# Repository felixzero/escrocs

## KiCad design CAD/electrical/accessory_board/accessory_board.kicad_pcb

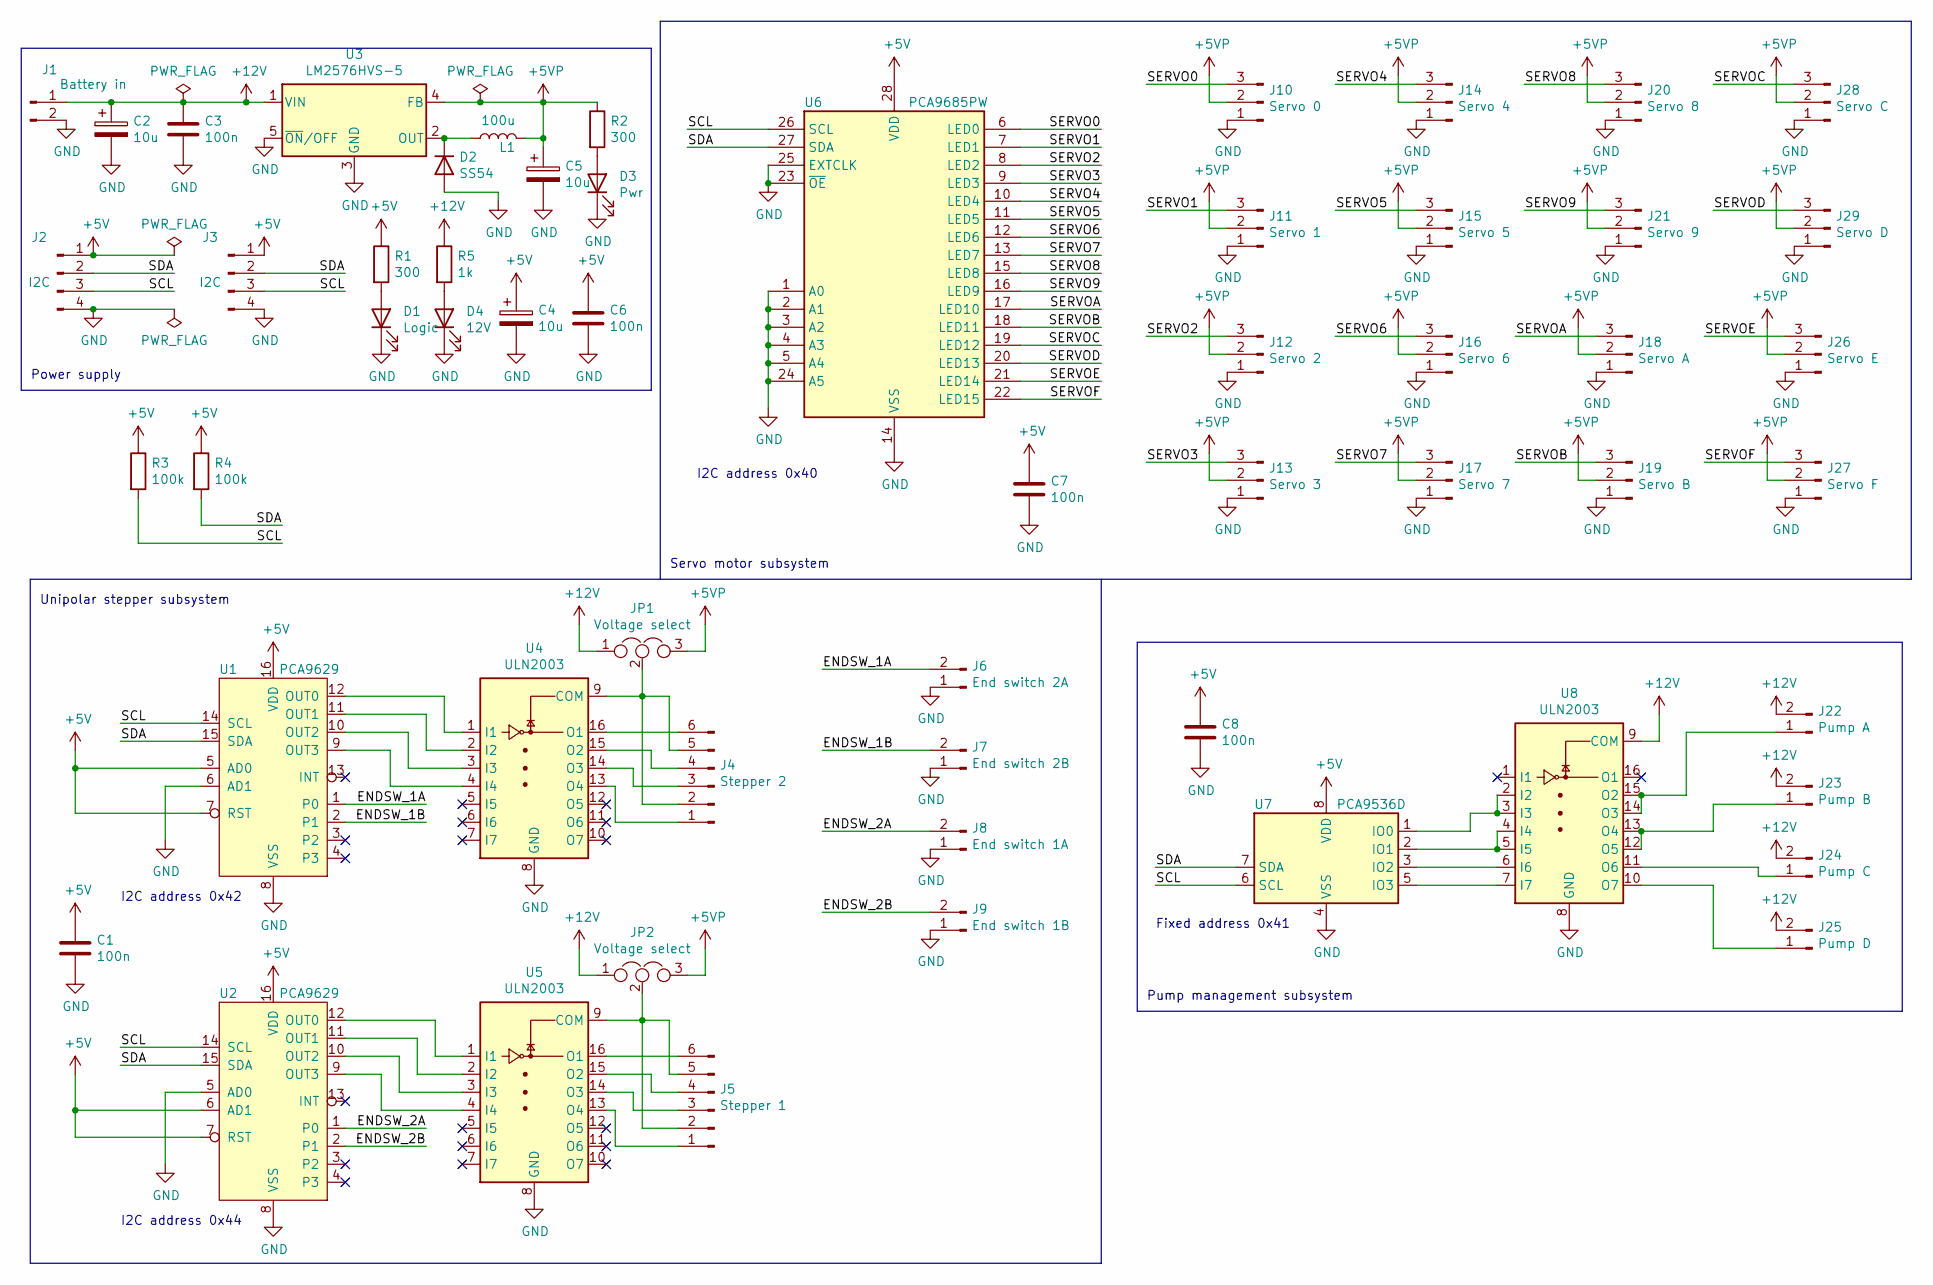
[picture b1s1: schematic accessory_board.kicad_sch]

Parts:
C1, C3, C6, C7, C8: 100n; C_1206_3216Metric_Pad1.33x1.80mm_HandSolder
C2, C4, C5: 10u; CP_Radial_D5.0mm_P2.00mm
D1: Logic; LED_D3.0mm
D2: SS54; D_SMB_Handsoldering
D3: Pwr; LED_D3.0mm
D4: 12V; LED_D3.0mm
J1: Battery in; BarrelJack_Horizontal
J2, J3: I2C; Molex_KK-254_AE-6410-04A_1x04_P2.54mm_Vertical
J4: Stepper 2; Molex_KK-254_AE-6410-06A_1x06_P2.54mm_Vertical
J5: Stepper 1; Molex_KK-254_AE-6410-06A_1x06_P2.54mm_Vertical
J6: End switch 2A; Molex_KK-254_AE-6410-02A_1x02_P2.54mm_Vertical
J7: End switch 2B; Molex_KK-254_AE-6410-02A_1x02_P2.54mm_Vertical
J8: End switch 1A; Molex_KK-254_AE-6410-02A_1x02_P2.54mm_Vertical
J9: End switch 1B; Molex_KK-254_AE-6410-02A_1x02_P2.54mm_Vertical
J10: Servo 0; Molex_KK-254_AE-6410-03A_1x03_P2.54mm_Vertical
J11: Servo 1; Molex_KK-254_AE-6410-03A_1x03_P2.54mm_Vertical
J12: Servo 2; Molex_KK-254_AE-6410-03A_1x03_P2.54mm_Vertical
J13: Servo 3; Molex_KK-254_AE-6410-03A_1x03_P2.54mm_Vertical
J14: Servo 4; Molex_KK-254_AE-6410-03A_1x03_P2.54mm_Vertical
J15: Servo 5; Molex_KK-254_AE-6410-03A_1x03_P2.54mm_Vertical
J16: Servo 6; Molex_KK-254_AE-6410-03A_1x03_P2.54mm_Vertical
J17: Servo 7; Molex_KK-254_AE-6410-03A_1x03_P2.54mm_Vertical
J18: Servo A; Molex_KK-254_AE-6410-03A_1x03_P2.54mm_Vertical
J19: Servo B; Molex_KK-254_AE-6410-03A_1x03_P2.54mm_Vertical
J20: Servo 8; Molex_KK-254_AE-6410-03A_1x03_P2.54mm_Vertical
J21: Servo 9; Molex_KK-254_AE-6410-03A_1x03_P2.54mm_Vertical
J22: Pump A; Molex_KK-254_AE-6410-02A_1x02_P2.54mm_Vertical
J23: Pump B; Molex_KK-254_AE-6410-02A_1x02_P2.54mm_Vertical
J24: Pump C; Molex_KK-254_AE-6410-02A_1x02_P2.54mm_Vertical
J25: Pump D; Molex_KK-254_AE-6410-02A_1x02_P2.54mm_Vertical
J26: Servo E; Molex_KK-254_AE-6410-03A_1x03_P2.54mm_Vertical
J27: Servo F; Molex_KK-254_AE-6410-03A_1x03_P2.54mm_Vertical
J28: Servo C; Molex_KK-254_AE-6410-03A_1x03_P2.54mm_Vertical
J29: Servo D; Molex_KK-254_AE-6410-03A_1x03_P2.54mm_Vertical
JP1, JP2: Voltage select; PinHeader_1x03_P2.54mm_Vertical
L1: 100u; L_Radial_D24.4mm_P23.70mm_muRATA_1400series
R1, R2: 300; R_1206_3216Metric_Pad1.30x1.75mm_HandSolder
R3, R4: 100k; R_1206_3216Metric_Pad1.30x1.75mm_HandSolder
R5: 1k; R_1206_3216Metric_Pad1.30x1.75mm_HandSolder
U1, U2: PCA9629; TSSOP-16_4.4x5mm_P0.65mm
U3: LM2576HVS-5; TO-263-5_TabPin3
U4, U5, U8: ULN2003; SO-16_3.9x9.9mm_P1.27mm
U6: PCA9685PW; TSSOP-28_4.4x9.7mm_P0.65mm
U7: PCA9536D; SOIC-8_3.9x4.9mm_P1.27mm

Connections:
+5V: C1.1, C4.1, C6.1, C7.1, C8.1, J2.1, J3.1, R1.1, R3.1, R4.1, U1.5 (AD0), U1.7 (RST), U1.16 (VDD), U2.6 (AD1), U2.7 (RST), U2.16 (VDD), U6.28 (VDD), U7.8 (VDD)
+5VP: C5.1, J10.2, J11.2, J12.2, J13.2, J14.2, J15.2, J16.2, J17.2, J18.2, J19.2, J20.2, J21.2, J26.2, J27.2, J28.2, J29.2, JP1.3, JP2.3, L1.2, R2.1, U3.4 (FB)
+12V: C2.1, C3.1, J1.1, J22.2, J23.2, J24.2, J25.2, JP1.1, JP2.1, R5.1, U3.1 (VIN), U8.9 (COM)
/ENDSW_1A: J6.2, U1.1 (P0)
/ENDSW_1B: J7.2, U1.2 (P1)
/ENDSW_2A: J8.2, U2.1 (P0)
/ENDSW_2B: J9.2, U2.2 (P1)
/SCL: J2.3, J3.3, R3.2, U1.14 (SCL), U2.14 (SCL), U6.26 (SCL), U7.6 (SCL)
/SDA: J2.2, J3.2, R4.2, U1.15 (SDA), U2.15 (SDA), U6.27 (SDA), U7.7 (SDA)
/SERVO0: J10.3, U6.6 (LED0)
/SERVO1: J11.3, U6.7 (LED1)
/SERVO2: J12.3, U6.8 (LED2)
/SERVO3: J13.3, U6.9 (LED3)
/SERVO4: J14.3, U6.10 (LED4)
/SERVO5: J15.3, U6.11 (LED5)
/SERVO6: J16.3, U6.12 (LED6)
/SERVO7: J17.3, U6.13 (LED7)
/SERVO8: J20.3, U6.15 (LED8)
/SERVO9: J21.3, U6.16 (LED9)
/SERVOA: J18.3, U6.17 (LED10)
/SERVOB: J19.3, U6.18 (LED11)
/SERVOC: J28.3, U6.19 (LED12)
/SERVOD: J29.3, U6.20 (LED13)
/SERVOE: J26.3, U6.21 (LED14)
/SERVOF: J27.3, U6.22 (LED15)
GND: C1.2, C2.2, C3.2, C4.2, C5.2, C6.2, C7.2, C8.2, D1.1 (K), D2.2 (A), D3.1 (K), D4.1 (K), J1.2, J2.4, J3.4, J6.1, J7.1, J8.1, J9.1, J10.1, J11.1, J12.1, J13.1, J14.1, J15.1, J16.1, J17.1, J18.1, J19.1, J20.1, J21.1, J26.1, J27.1, J28.1, J29.1, U1.6 (AD1), U1.8 (VSS), U2.5 (AD0), U2.8 (VSS), U3.3 (GND), U3.5 (~ON/OFF), U4.8 (GND), U5.8 (GND), U6.1 (A0), U6.2 (A1), U6.3 (A2), U6.4 (A3), U6.5 (A4), U6.14 (VSS), U6.23 (~OE), U6.24 (A5), U6.25 (EXTCLK), U7.4 (VSS), U8.8 (GND)
unnamed: D1.2 (A), R1.2
unnamed: D2.1 (K), L1.1, U3.2 (OUT)
unnamed: D3.2 (A), R2.2
unnamed: D4.2 (A), R5.2
unnamed: J4.1, U4.13 (O4)
unnamed: J4.2, J4.5, JP1.2, U4.9 (COM)
unnamed: J4.3, U4.14 (O3)
unnamed: J4.4, U4.15 (O2)
unnamed: J4.6, U4.16 (O1)
unnamed: J5.1, U5.13 (O4)
unnamed: J5.2, J5.5, JP2.2, U5.9 (COM)
unnamed: J5.3, U5.14 (O3)
unnamed: J5.4, U5.15 (O2)
unnamed: J5.6, U5.16 (O1)
unnamed: J22.1, U8.14 (O3), U8.15 (O2)
unnamed: J23.1, U8.12 (O5), U8.13 (O4)
unnamed: J24.1, U8.11 (O6)
unnamed: J25.1, U8.10 (O7)
unnamed: U1.9 (OUT3), U4.4 (I4)
unnamed: U1.10 (OUT2), U4.3 (I3)
unnamed: U1.11 (OUT1), U4.2 (I2)
unnamed: U1.12 (OUT0), U4.1 (I1)
unnamed: U2.9 (OUT3), U5.4 (I4)
unnamed: U2.10 (OUT2), U5.3 (I3)
unnamed: U2.11 (OUT1), U5.2 (I2)
unnamed: U2.12 (OUT0), U5.1 (I1)
unnamed: U7.1 (IO0), U8.2 (I2), U8.3 (I3)
unnamed: U7.2 (IO1), U8.4 (I4), U8.5 (I5)
unnamed: U7.3 (IO2), U8.6 (I6)
unnamed: U7.5 (IO3), U8.7 (I7)

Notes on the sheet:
Fixed address 0x41
I2C address 0x42
I2C address 0x40
I2C address 0x44
Pump management subsystem
Power supply
Servo motor subsystem
Unipolar stepper subsystem

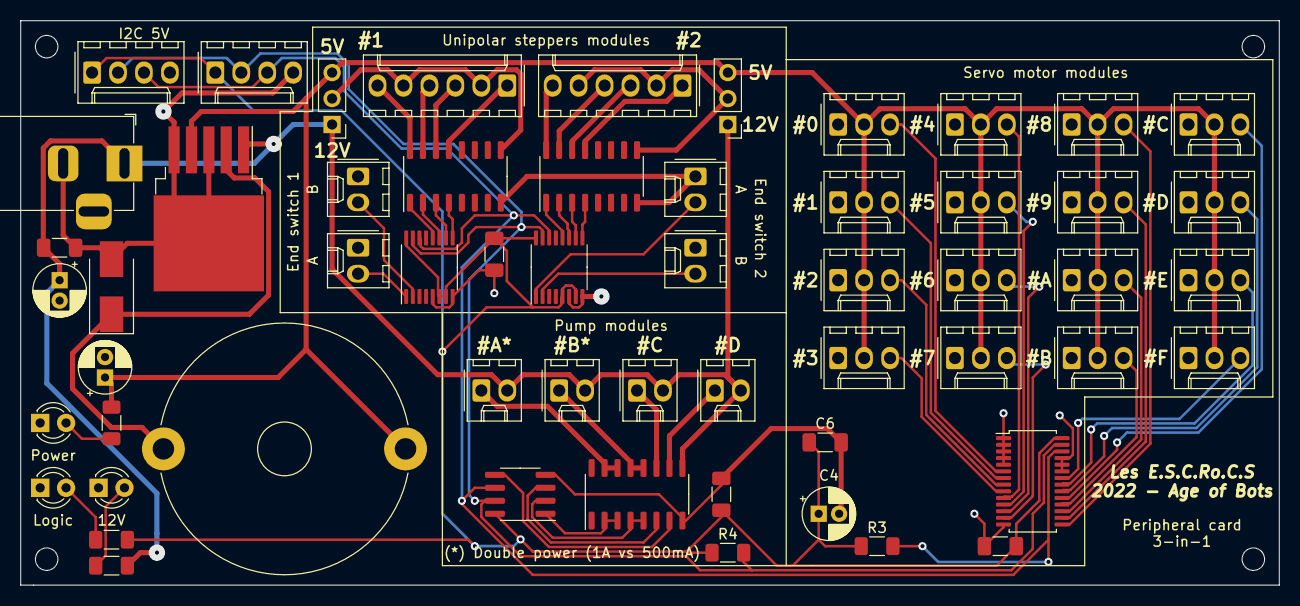
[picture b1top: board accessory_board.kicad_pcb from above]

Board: 2 copper layers, 123.2 x 55.2 mm, 57 parts (0 on the bottom side), 56 nets.

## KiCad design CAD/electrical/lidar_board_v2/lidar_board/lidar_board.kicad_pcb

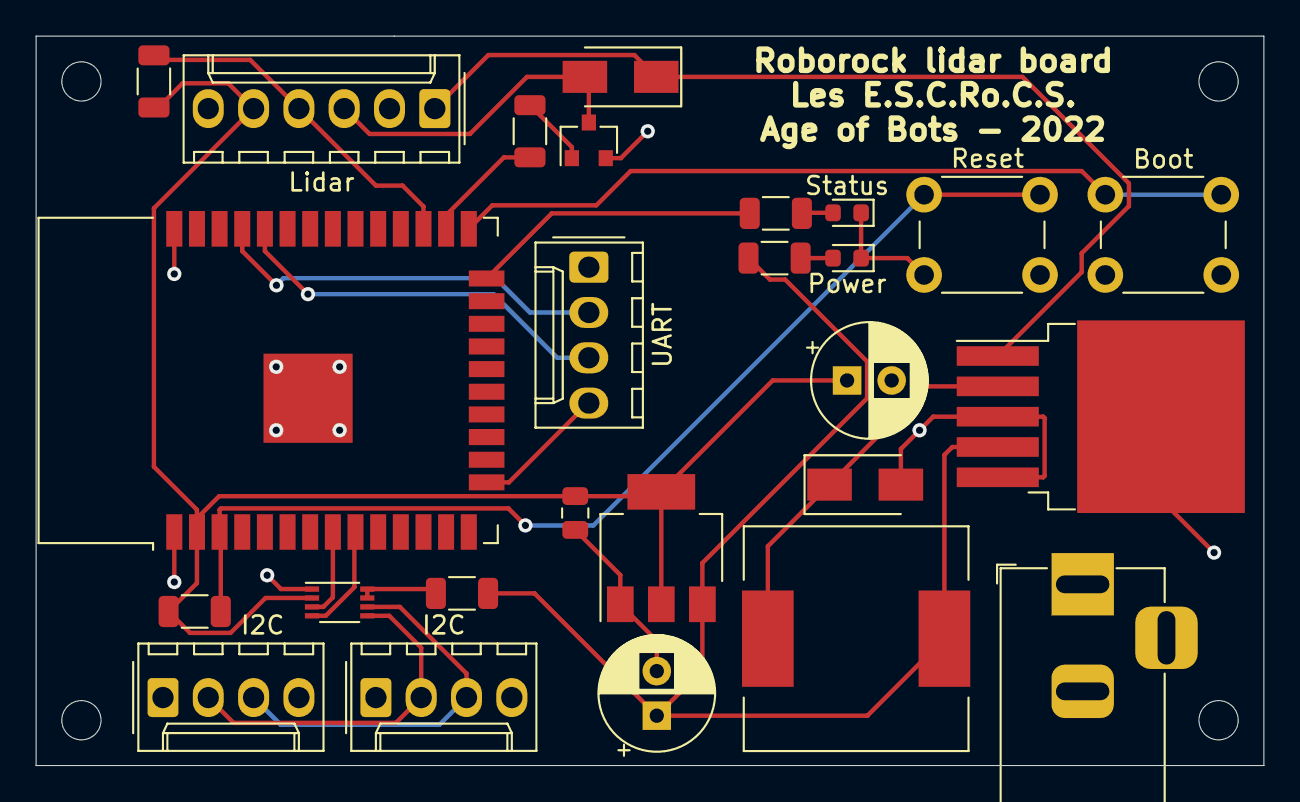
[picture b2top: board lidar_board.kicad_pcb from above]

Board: 2 copper layers, 68.8 x 40.9 mm, 26 parts (0 on the bottom side), 21 nets.

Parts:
Boot: Boot; SW_PUSH_6mm
C1, C2: 10u; CP_Radial_D6.3mm_P2.50mm
C3: 100n; C_0805_2012Metric
D1, D4: SS54; D_SMA
I2C, I2C#2: I2C bus; Molex_KK-254_AE-6410-04A_1x04_P2.54mm_Vertical
J1: 12V in; BarrelJack_Horizontal
L1: 100u; L_12x12mm_H6mm
Lidar: Lidar connector; Molex_KK-254_AE-6410-06A_1x06_P2.54mm_Vertical
Power: PWR; LED_0603_1608Metric
Q1: AO3400A; SOT-23
R1: 100k; R_1206_3216Metric
R2, R4: 100; R_1206_3216Metric
R3: 10k; R_1206_3216Metric
R5: 470; R_1206_3216Metric
R6: 1k; R_1206_3216Metric
Reset: Reset; SW_PUSH_6mm
Status: Status; LED_0603_1608Metric
U1: LM2576HVS-5; TO-263-5_TabPin3
U2: PCA9306DC1; VSSOP-8_2.3x2mm_P0.5mm
U3: AMS1117-3.3; SOT-223-3_TabPin2
U4: ESP32-WROOM-32
UART: UART; Molex_KK-254_AE-6410-04A_1x04_P2.54mm_Vertical

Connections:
+3V3: C2.1, C3.1, Lidar.5, R3.1, R6.2, U2.2, U3.2, U4.2
+5V: C1.1, L1.2, R1.1, R2.1, U1.4, U3.3
+12V: D4.1, Lidar.1, U1.1
/I2C_SCL: U2.3, U4.8
/I2C_SDA: U2.4, U4.9
/LDS_TX: Lidar.4, R6.1, U4.27
/MOT-: D4.2, Lidar.3, Q1.3
/MOT_PWM: R5.2, U4.26
/UART_MISO: U4.35, UART.2
/UART_MOSI: U4.34, UART.3
GND: Boot.2, C1.2, C2.2, C3.2, D1.2, I2C.4, I2C#2.4, J1.2, Lidar.2, Power.1, Q1.2, Reset.2, Status.1, U1.3, U1.5, U2.1, U3.1, U4.1, U4.15, U4.38, U4.39, UART.4
unnamed: D1.1, L1.1, U1.2
unnamed: Power.2, R2.2
unnamed: R4.2, Status.2
unnamed: I2C.2, I2C#2.2, U2.5
unnamed: I2C.3, I2C#2.3, U2.6
unnamed: Q1.1, R5.1
unnamed: R1.2, U2.7, U2.8
unnamed: R3.2, Reset.1, U4.3
unnamed: R4.1, U4.24
unnamed: Boot.1, U4.25

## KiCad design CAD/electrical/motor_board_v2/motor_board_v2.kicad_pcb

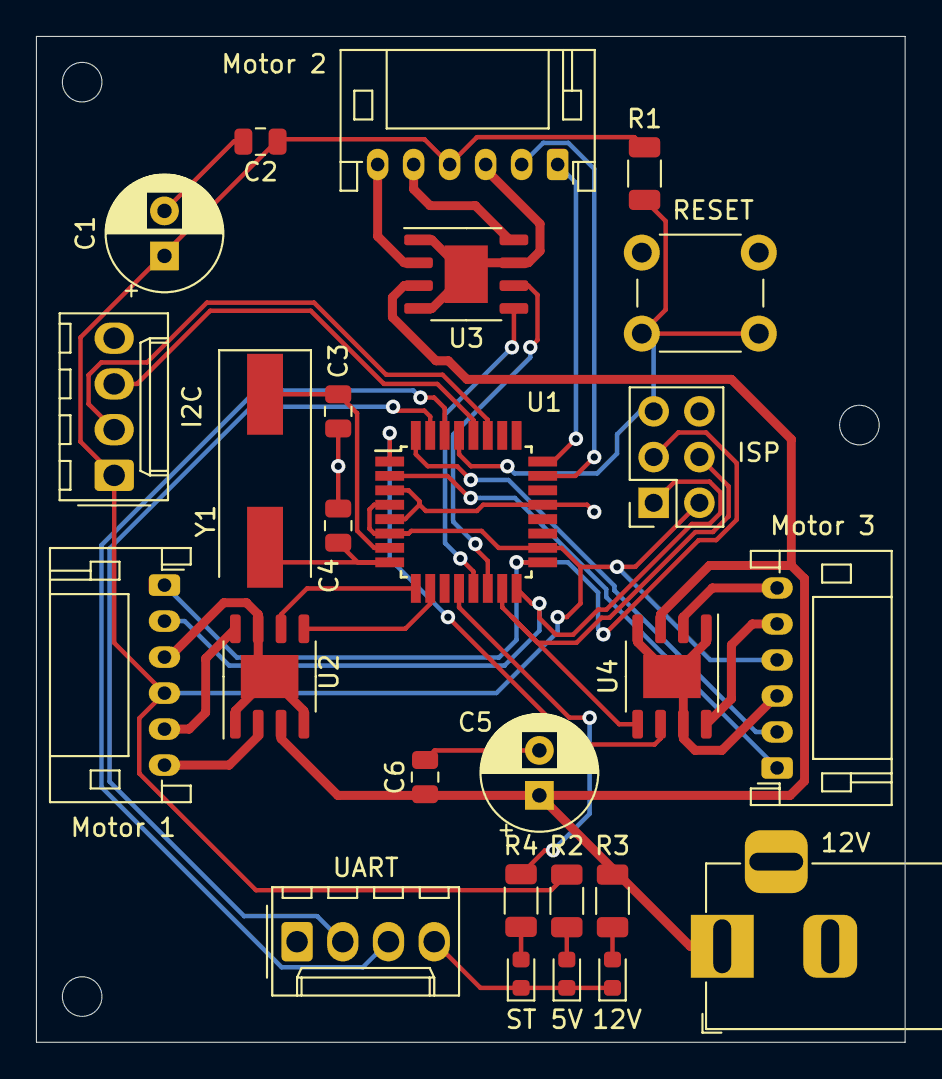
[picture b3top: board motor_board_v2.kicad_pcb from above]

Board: 2 copper layers, 48.3 x 55.9 mm, 26 parts (0 on the bottom side), 32 nets.

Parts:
5V: 5V; LED_0603_1608Metric
12V: 12V in; BarrelJack_Horizontal
12V#2: 12V; LED_0603_1608Metric
C1, C5: 10u; CP_Radial_D6.3mm_P2.50mm
C2, C6: 100n; C_0805_2012Metric
C3, C4: 22p; C_0805_2012Metric
I2C: I2C; Molex_KK-254_AE-6410-04A_1x04_P2.54mm_Vertical
ISP: ISP; PinSocket_2x03_P2.54mm_Vertical
Motor 1: Motor 1; JST_PH_S6B-PH-K_1x06_P2.00mm_Horizontal
Motor 2: Motor 2; JST_PH_S6B-PH-K_1x06_P2.00mm_Horizontal
Motor 3: Motor 3; JST_PH_S6B-PH-K_1x06_P2.00mm_Horizontal
R1: 10k; R_1206_3216Metric
R2, R3, R4: 470; R_1206_3216Metric
RESET: SW_Push; SW_PUSH_6mm
ST: Status; LED_0603_1608Metric
U1: ATmega328P-AU; TQFP-32_7x7mm_P0.8mm
U2, U3, U4: BD62130AEFJ; HTSOP-8-1EP_3.9x4.9mm_P1.27mm_EP2.4x3.2mm
UART: UART; Molex_KK-254_AE-6410-04A_1x04_P2.54mm_Vertical
Y1: 16MHz; Crystal_SMD_HC49-SD

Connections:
+5V: C1.1, C2.1, I2C.1, ISP.2, Motor 1.4, Motor 2.4, Motor 3.4, R1.1, R2.1, U1.4, U1.6, U1.18
+12V: 12V.1, C5.1, C6.1, R3.1, U2.3, U3.3, U4.3
/ENC1A: ISP.1, Motor 1.2, U1.16
/ENC1B: ISP.3, Motor 1.1, U1.17
/ENC2A: Motor 2.2, U1.23
/ENC2B: Motor 2.1, U1.24
/ENC3A: Motor 3.2, U1.32
/ENC3B: Motor 3.1, U1.2
/I2C_SCL: I2C.3, U1.28
/I2C_SDA: I2C.2, U1.27
/OC0A: U1.10, U2.5
/OC0B: U1.9, U2.6
/OC1A: U1.13, U3.5
/OC1B: U1.14, U3.6
/OC2A: ISP.4, U1.15, U4.5
/OC2B: U1.1, U4.6
/RST: ISP.5, R1.2, RESET.1, U1.29
/STATUS: R4.1, U1.12
/UART_RX: U1.30, UART.3
/UART_TX: U1.31, UART.2
/XTAL1: C3.1, U1.7, Y1.1
/XTAL2: C4.1, U1.8, Y1.2
GND: 5V.1, 12V.2, 12V#2.1, C1.2, C2.2, C3.2, C4.2, C5.2, C6.2, I2C.4, ISP.6, Motor 1.3, Motor 2.3, Motor 3.3, RESET.2, ST.1, U1.3, U1.5, U1.21, U2.1, U2.4, U2.7, U2.9, U3.1, U3.4, U3.7, U3.9, U4.1, U4.4, U4.7, U4.9, UART.4
unnamed: 5V.2, R2.2
unnamed: 12V#2.2, R3.2
unnamed: R4.2, ST.2
unnamed: Motor 1.5, U2.8
unnamed: Motor 1.6, U2.2
unnamed: Motor 2.5, U3.8
unnamed: Motor 2.6, U3.2
unnamed: Motor 3.5, U4.8
unnamed: Motor 3.6, U4.2

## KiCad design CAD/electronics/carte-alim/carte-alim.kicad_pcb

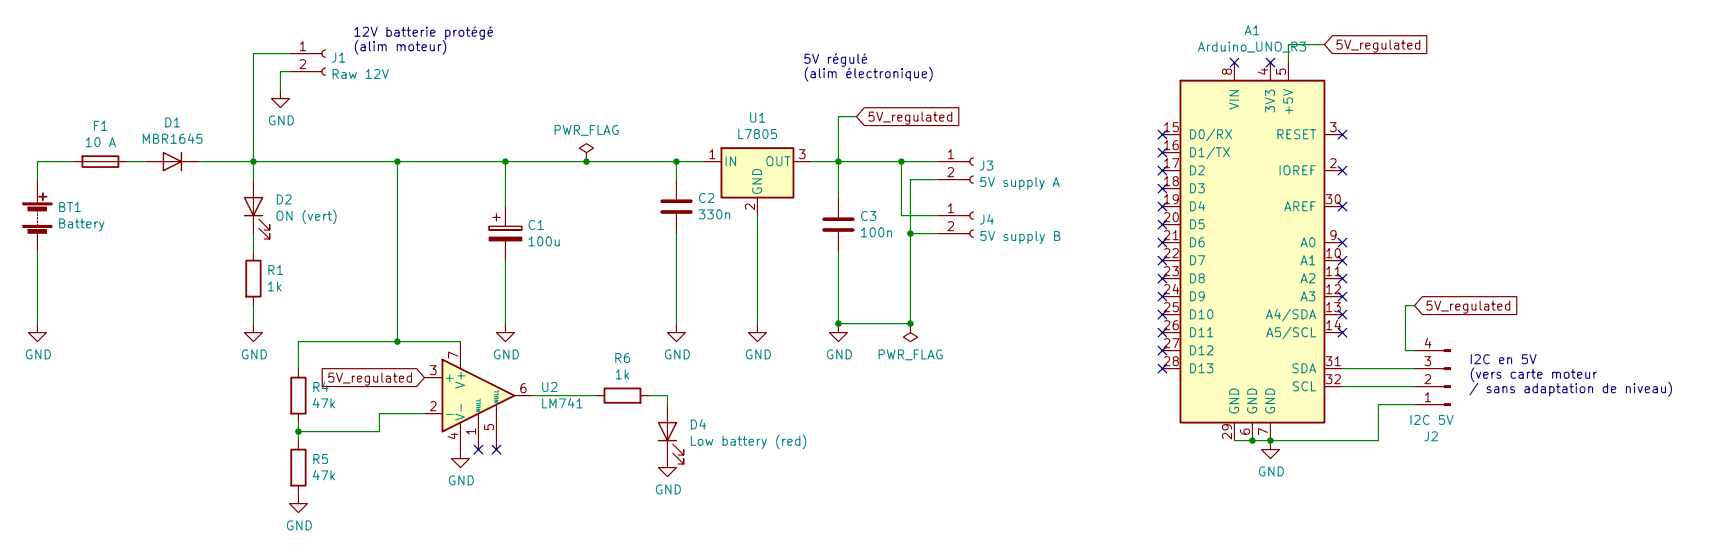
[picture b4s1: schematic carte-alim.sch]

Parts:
A1: Arduino_UNO_R3
BT1: Battery; SolderWirePad_1x02_P5.08mm_Drill1.5mm
C1: 100u; C_Radial_D10.0mm_H16.0mm_P5.00mm
C2: 330n; C_Rect_L9.0mm_W3.3mm_P7.50mm_MKT
C3: 100n; C_Rect_L9.0mm_W3.3mm_P7.50mm_MKT
D1: MBR1645; TO-126-2_Horizontal_TabDown
D2: ON (vert); LED_D3.0mm
D4: Low battery (red); LED_D3.0mm
F1: 10 A; Fuseholder_Cylinder-5x20mm_Stelvio-Kontek_PTF78_Horizontal_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
J1: Raw 12V; SolderWirePad_1x02_P5.08mm_Drill1.5mm
J2: I2C 5V; PinHeader_1x04_P2.54mm_Vertical
J3: 5V supply A; PinHeader_1x02_P2.54mm_Vertical
J4: 5V supply B; PinHeader_1x02_P2.54mm_Vertical
R1, R6: 1k; R_Axial_DIN0207_L6.3mm_D2.5mm_P10.16mm_Horizontal
R4, R5: 47k; R_Axial_DIN0207_L6.3mm_D2.5mm_P10.16mm_Horizontal
U1: L7805; TO-220-3_Horizontal_TabDown
U2: LM741; DIP-8_W7.62mm

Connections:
5V_regulated: A1.5 (+5V), C3.1, J2.4, J3.1, J4.1, U1.3 (OUT), U2.3 (+)
GND: A1.6 (GND), A1.7 (GND), A1.29 (GND), BT1.2 (-), C1.2, C2.2, C3.2, D4.1 (K), J1.2, J2.1, J3.2, J4.2, R1.2, R5.2, U1.2 (GND), U2.4 (V-)
unnamed: A1.31 (SDA), J2.3
unnamed: A1.32 (SCL), J2.2
unnamed: BT1.1 (+), F1.2
unnamed: C1.1, C2.1, D1.1 (K), D2.2 (A), J1.1, R4.1, U1.1 (IN), U2.7 (V+)
unnamed: D1.2 (A), F1.1
unnamed: D2.1 (K), R1.1
unnamed: D4.2 (A), R6.2
unnamed: R4.2, R5.1, U2.2 (-)
unnamed: R6.1, U2.6

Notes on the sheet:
I2C en 5V (vers carte moteur / sans adaptation de niveau)
12V batterie protégé (alim moteur)
5V régulé (alim électronique)

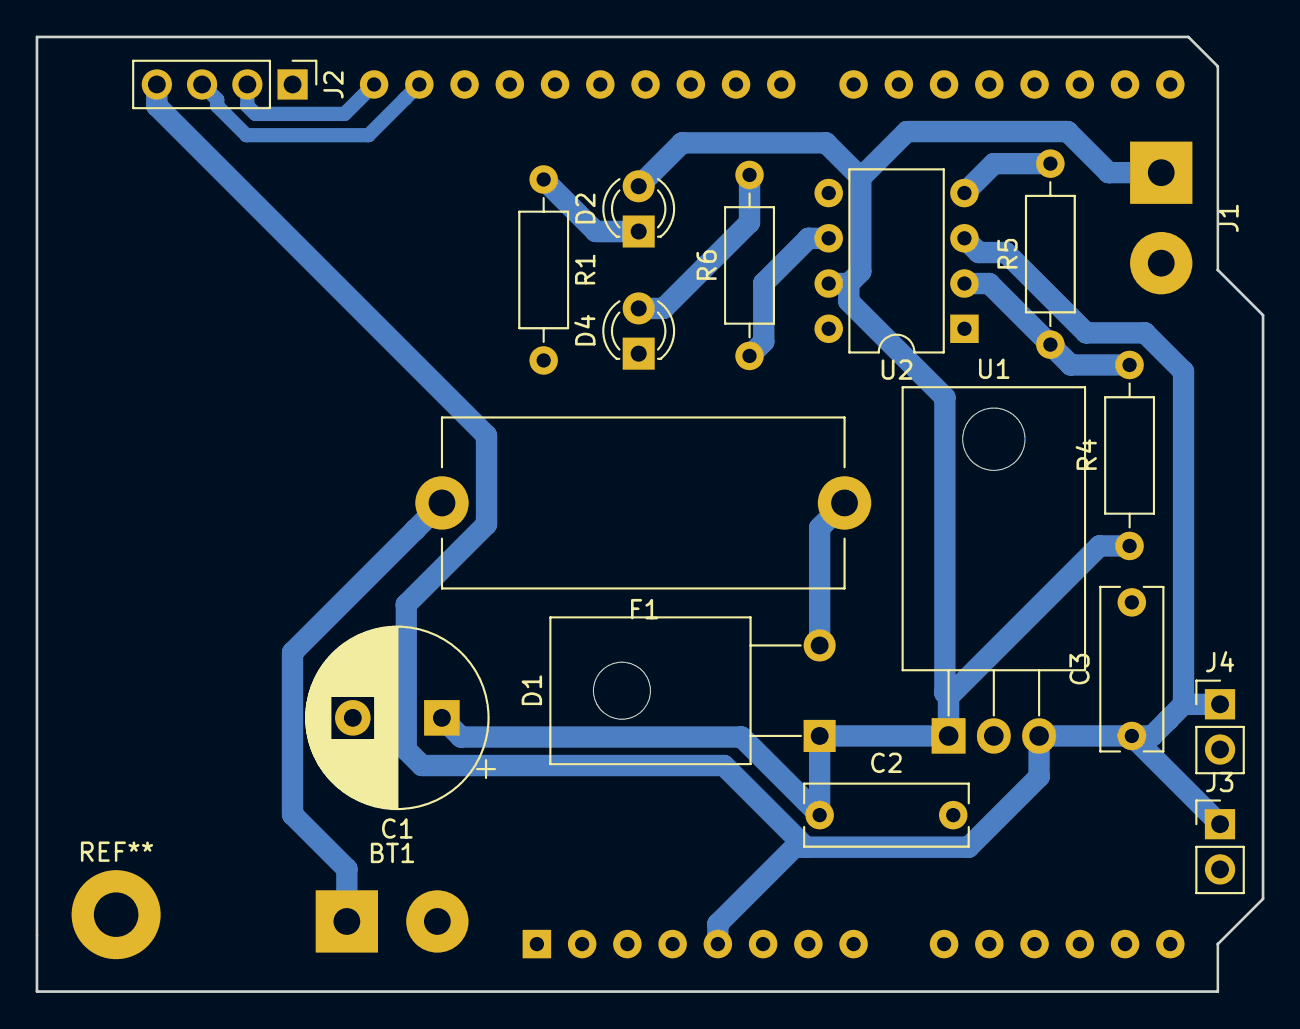
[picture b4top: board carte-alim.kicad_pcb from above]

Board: 2 copper layers, 68.8 x 53.6 mm, 19 parts (1 on the bottom side), 11 nets.

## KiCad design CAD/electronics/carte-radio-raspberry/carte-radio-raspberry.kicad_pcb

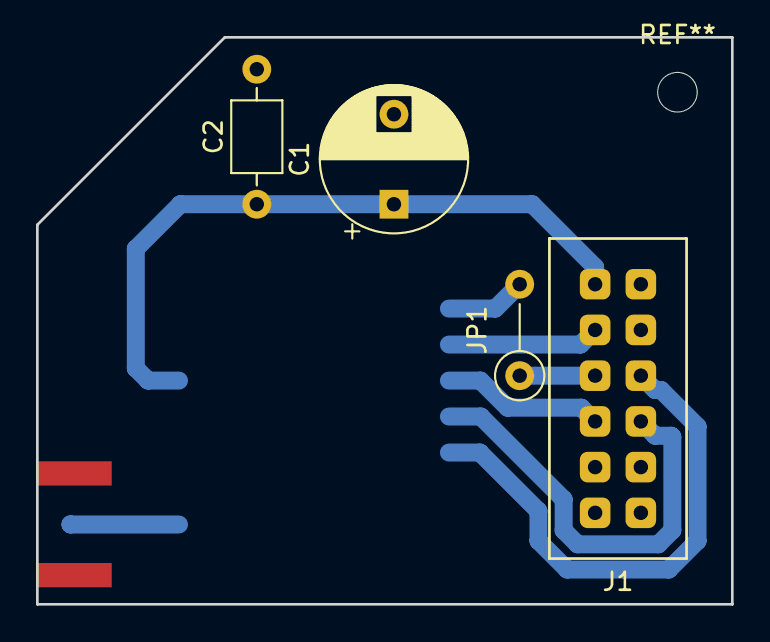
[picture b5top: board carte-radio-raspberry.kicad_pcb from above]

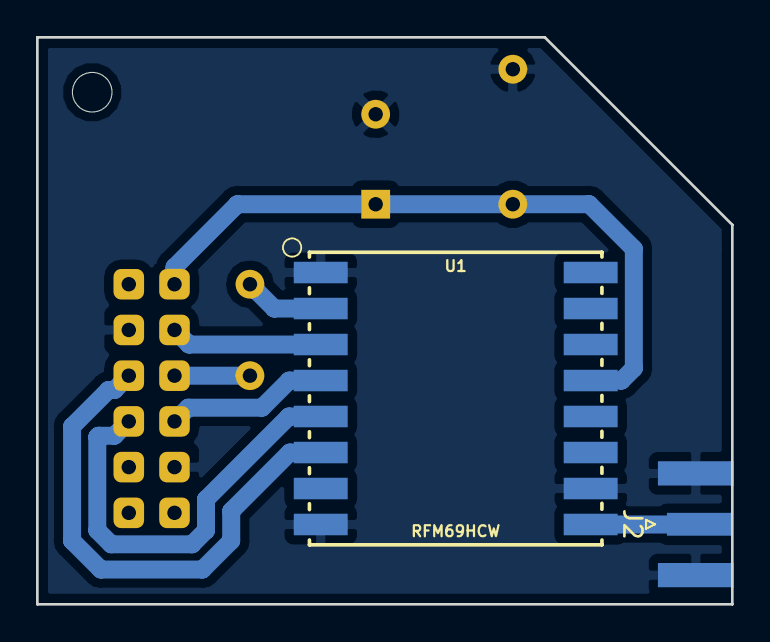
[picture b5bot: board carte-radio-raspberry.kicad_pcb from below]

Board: 2 copper layers, 38.6 x 31.5 mm, 6 parts (2 on the bottom side), 9 nets.

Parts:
C1: CP; CP_Radial_D8.0mm_P5.00mm
C2: C; C_Axial_L3.8mm_D2.6mm_P7.50mm_Horizontal
J1: Raspberry_Pi_2_3; raspi-spi
J2: Conn_Coaxial; SMA_Samtec_SMA-J-P-H-ST-EM1_EdgeMount
JP1: Jumper; R_Axial_DIN0207_L6.3mm_D2.5mm_P5.08mm_Vertical
U1: RFM69HCW; RFM69HCW-XXXS2

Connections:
3V3: C1.1, C2.1, J1.17, U1.13
GND: C1.2, C2.2, J1.20, J1.25, J2.2, U1.1, U1.8, U1.10
unnamed: J1.19, U1.3
unnamed: J1.21, JP1.1
unnamed: J1.23, U1.4
unnamed: J1.24, U1.5
unnamed: J2.1, U1.9
unnamed: JP1.2, U1.2
RESET: J1.22, U1.6

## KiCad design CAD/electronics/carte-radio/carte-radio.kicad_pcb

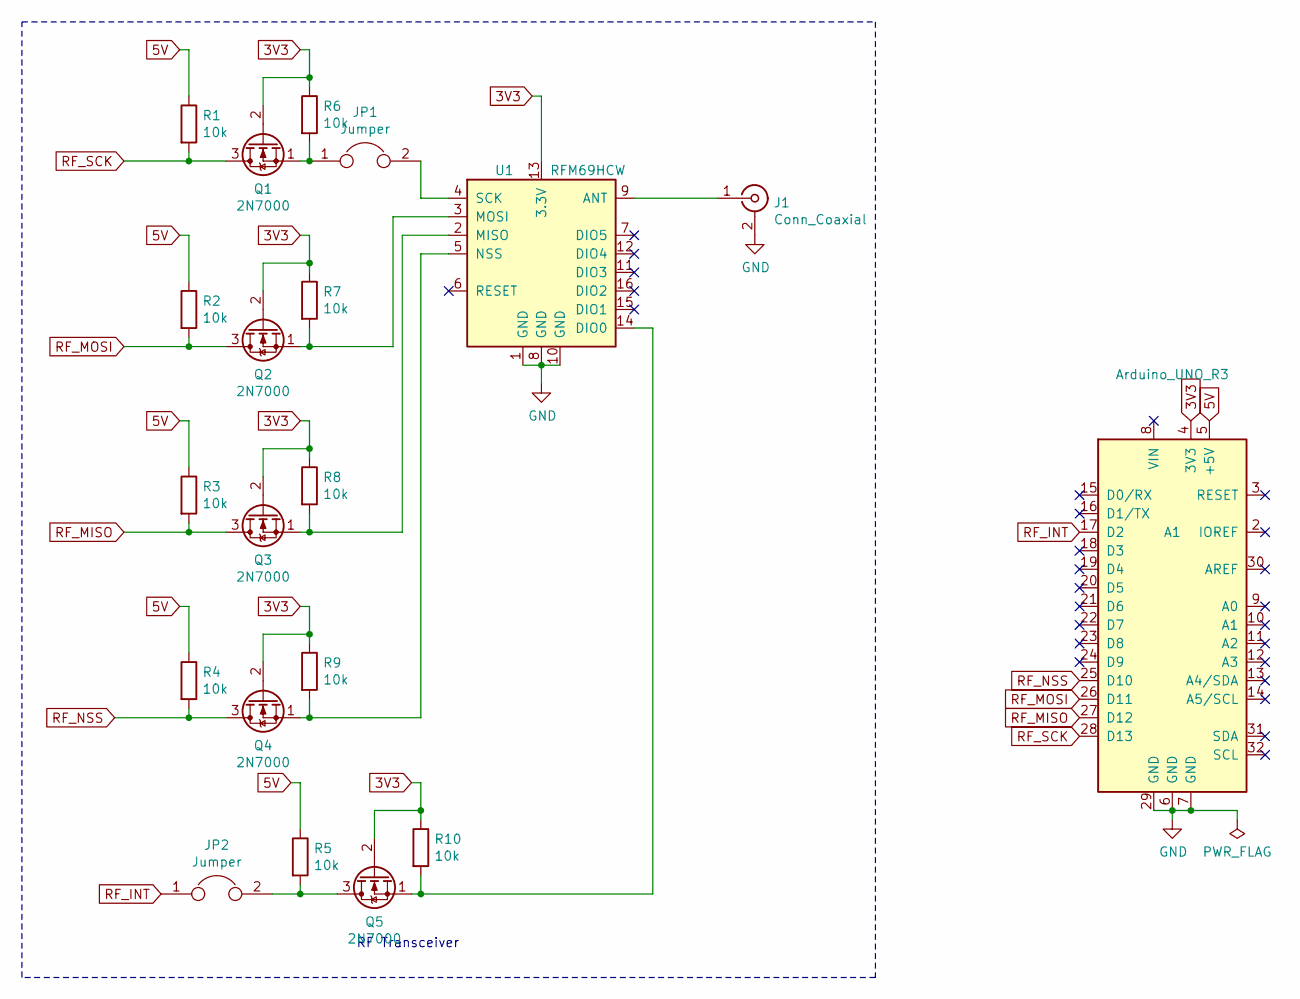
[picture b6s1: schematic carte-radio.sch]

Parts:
A1: Arduino_UNO_R3
J1: Conn_Coaxial; SMA_Samtec_SMA-J-P-H-ST-EM1_EdgeMount
JP1: Jumper; R_Axial_DIN0309_L9.0mm_D3.2mm_P12.70mm_Horizontal
JP2: Jumper; R_Axial_DIN0207_L6.3mm_D2.5mm_P15.24mm_Horizontal
Q1, Q2, Q3, Q4, Q5: 2N7000; TO-92_Inline_Wide
R1, R2, R3, R4, R5, R6, R7, R8, R9, R10: 10k; R_Axial_DIN0207_L6.3mm_D2.5mm_P7.62mm_Horizontal
U1: RFM69HCW; RFM69HCW-XXXS2

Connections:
3V3: A1.4 (3V3), Q1.2 (G), Q2.2 (G), Q3.2 (G), Q4.2 (G), Q5.2 (G), R6.1, R7.1, R8.1, R9.1, R10.1, U1.13 (3.3V)
5V: A1.5 (+5V), R1.1, R2.1, R3.1, R4.1, R5.1
GND: A1.6 (GND), A1.7 (GND), A1.29 (GND), J1.2 (Ext), U1.1 (GND), U1.8 (GND), U1.10 (GND)
unnamed: J1.1 (In), U1.9 (ANT)
unnamed: JP1.1, Q1.1 (S), R6.2
unnamed: JP1.2, U1.4 (SCK)
unnamed: JP2.2, Q5.3 (D), R5.2
unnamed: Q2.1 (S), R7.2, U1.3 (MOSI)
unnamed: Q3.1 (S), R8.2, U1.2 (MISO)
unnamed: Q4.1 (S), R9.2, U1.5 (NSS)
unnamed: Q5.1 (S), R10.2, U1.14 (DIO0)
RF_INT: A1.17 (D2), JP2.1
RF_MISO: A1.27 (D12), Q3.3 (D), R3.2
RF_MOSI: A1.26 (D11), Q2.3 (D), R2.2
RF_NSS: A1.25 (D10), Q4.3 (D), R4.2
RF_SCK: A1.28 (D13), Q1.3 (D), R1.2

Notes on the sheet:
RF Transceiver

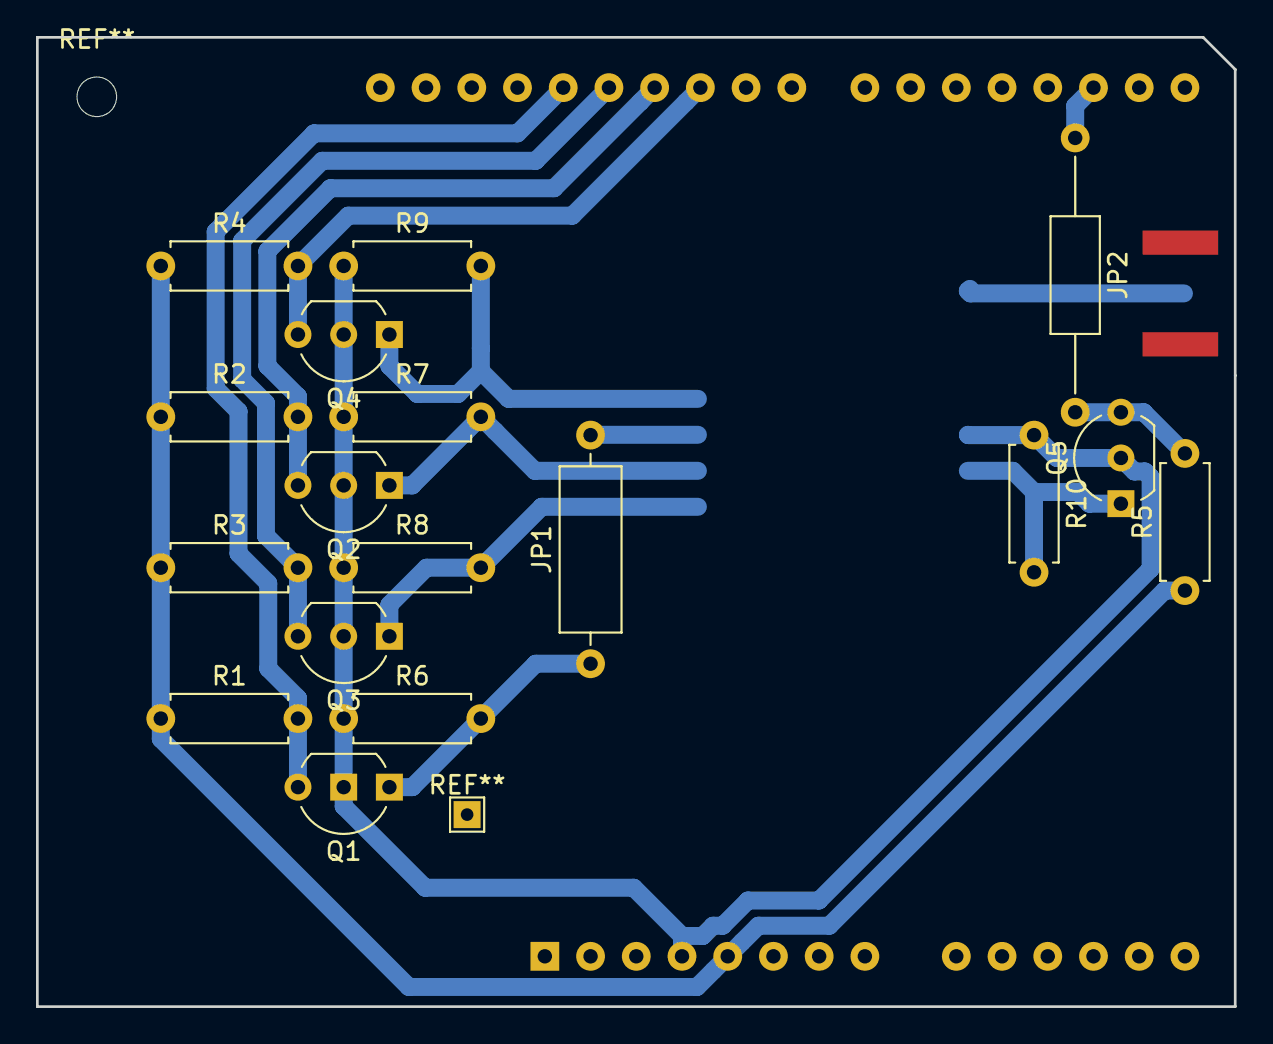
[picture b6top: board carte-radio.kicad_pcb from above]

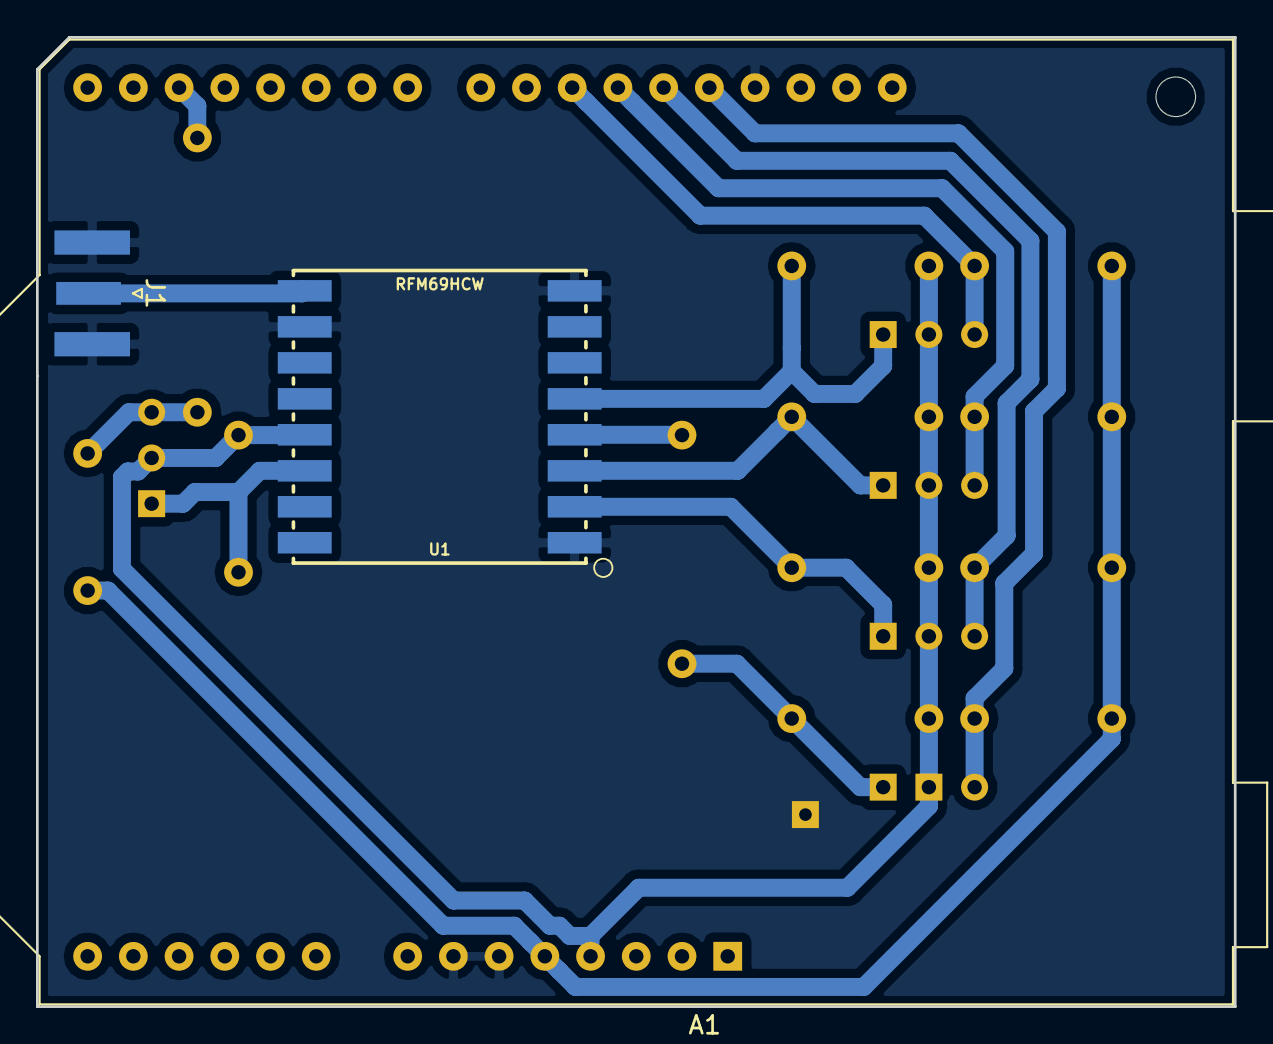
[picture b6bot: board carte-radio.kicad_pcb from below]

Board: 2 copper layers, 66.5 x 53.8 mm, 20 parts (3 on the bottom side), 16 nets.

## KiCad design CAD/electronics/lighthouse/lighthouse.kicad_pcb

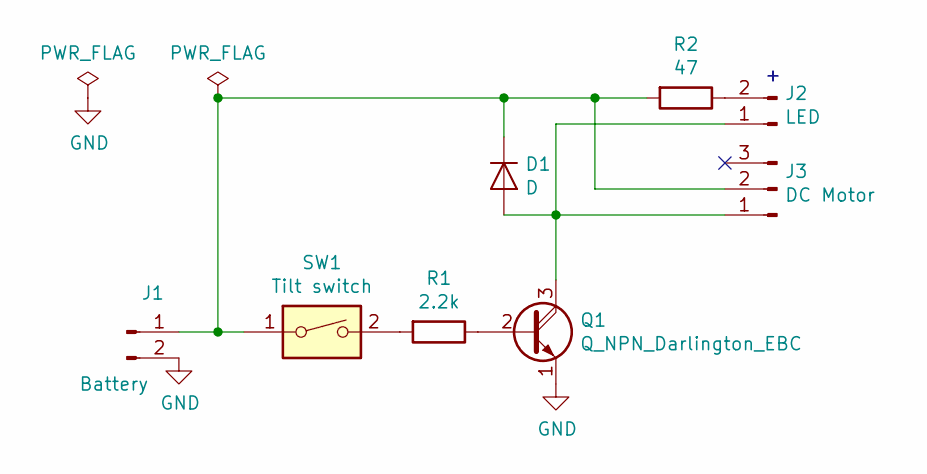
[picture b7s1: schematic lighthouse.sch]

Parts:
D1: D; D_DO-35_SOD27_P10.16mm_Horizontal
J1: Battery; Molex_KK-254_AE-6410-02A_1x02_P2.54mm_Vertical
J2: LED; Molex_KK-254_AE-6410-02A_1x02_P2.54mm_Vertical
J3: DC Motor; Molex_KK-254_AE-6410-03A_1x03_P2.54mm_Vertical
Q1: Q_NPN_Darlington_EBC; TO-92L_Inline_Wide
R1: 2.2k; R_Axial_DIN0204_L3.6mm_D1.6mm_P7.62mm_Horizontal
R2: 47; R_Axial_DIN0204_L3.6mm_D1.6mm_P7.62mm_Horizontal
SW1: Tilt switch; Mercury tilt switch

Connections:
GND: J1.2, Q1.1 (E)
unnamed: D1.1 (K), J1.1, J3.2, R2.2, SW1.1
unnamed: D1.2 (A), J2.1, J3.1, Q1.3 (C)
unnamed: J2.2, R2.1
unnamed: Q1.2 (B), R1.1
unnamed: R1.2, SW1.2

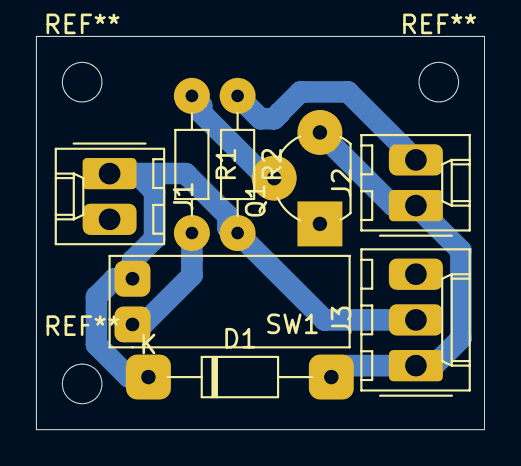
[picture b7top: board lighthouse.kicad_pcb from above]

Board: 2 copper layers, 24.9 x 21.8 mm, 8 parts (0 on the bottom side), 6 nets.
